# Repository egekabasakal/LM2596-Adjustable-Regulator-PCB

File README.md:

# LM2596 Adjustable Regulator PCB V0.1.0

Custom PCB design of an adjustable buck converter using LM2596S-ADJ.

## Features
- Input reverse-polarity protection (SB560 diode)
- Output LED indicator with series resistor
- Adjustable feedback via 3296W potentiometer
- Test pads for IN+/IN− and OUT+/OUT−
- 2-pin terminal blocks for input and output
- Barrel jack connector (optional)

## Files
- `schematic/` → KiCad schematic files
- `pcb/` → KiCad PCB layout
- `docs/` → images (schematic, layout, 3D)

## License
MIT

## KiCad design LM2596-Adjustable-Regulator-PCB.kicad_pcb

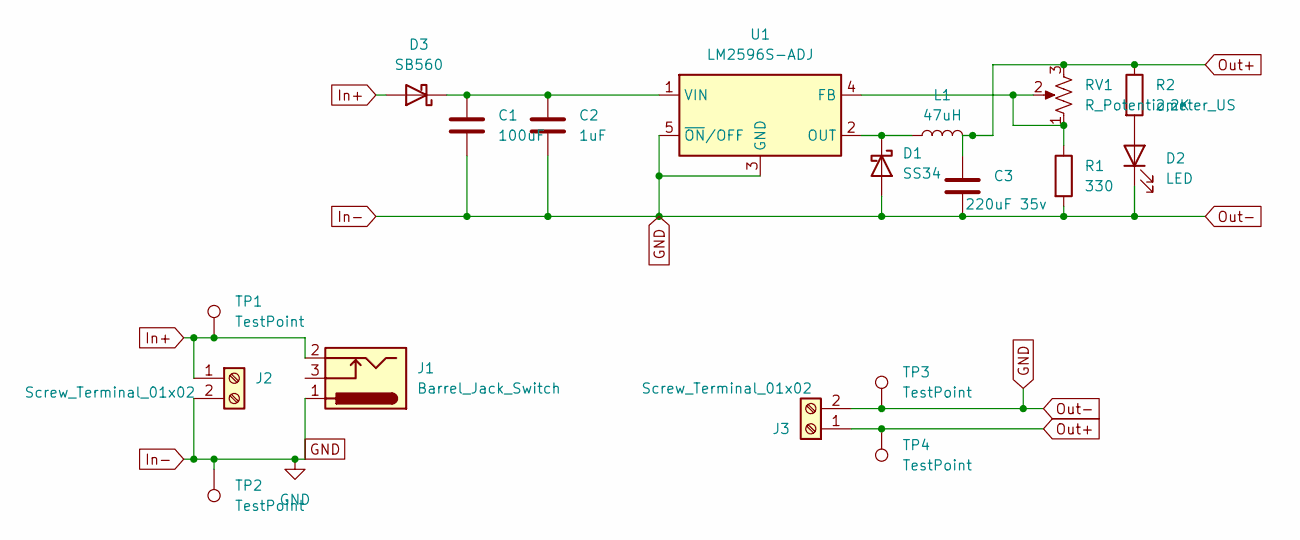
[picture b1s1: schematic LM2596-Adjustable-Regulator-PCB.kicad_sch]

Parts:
C1: 100uF; C_Elec_6.3x7.7
C2: 1uF; C_0805_2012Metric
C3: 220uF 35v; C_Elec_6.3x7.7
D1: SS34; D_SMA
D2: LED; LED_0201_0603Metric
D3: SB560; D_DO-201AD_P15.24mm_Horizontal
J1: Barrel_Jack_Switch; BarrelJack_CUI_PJ-063AH_Horizontal
J2, J3: Screw_Terminal_01x02; TerminalBlock_bornier-2_P5.08mm
L1: 47uH; L_12x12mm_H4.5mm
R1: 330; R_Axial_DIN0204_L3.6mm_D1.6mm_P2.54mm_Vertical
R2: 2,2K; R_Axial_DIN0204_L3.6mm_D1.6mm_P2.54mm_Vertical
RV1: R_Potentiometer_US; Potentiometer_Bourns_3269X_Horizontal
TP1, TP2, TP3, TP4: TestPoint; Pin_D1.4mm_L8.5mm_W2.8mm_FlatFork
U1: LM2596S-ADJ; TO-263-5_TabPin3

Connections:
GND: C1.2, C2.2, C3.2, D1.2 (A), D2.1 (K), J1.1, J2.2, J3.2, R1.2, TP2.1, TP3.1, U1.3 (GND), U1.5 (~ON/OFF)
In+: D3.2 (A), J1.2, J2.1, TP1.1
unnamed: D1.1 (K), L1.1, U1.2 (OUT)
unnamed: D2.2 (A), R2.2
unnamed: C1.1, C2.1, D3.1 (K), U1.1 (VIN)
unnamed: R1.1, RV1.1, RV1.2, U1.4 (FB)
Out+: C3.1, J3.1, L1.2, R2.1, RV1.3, TP4.1

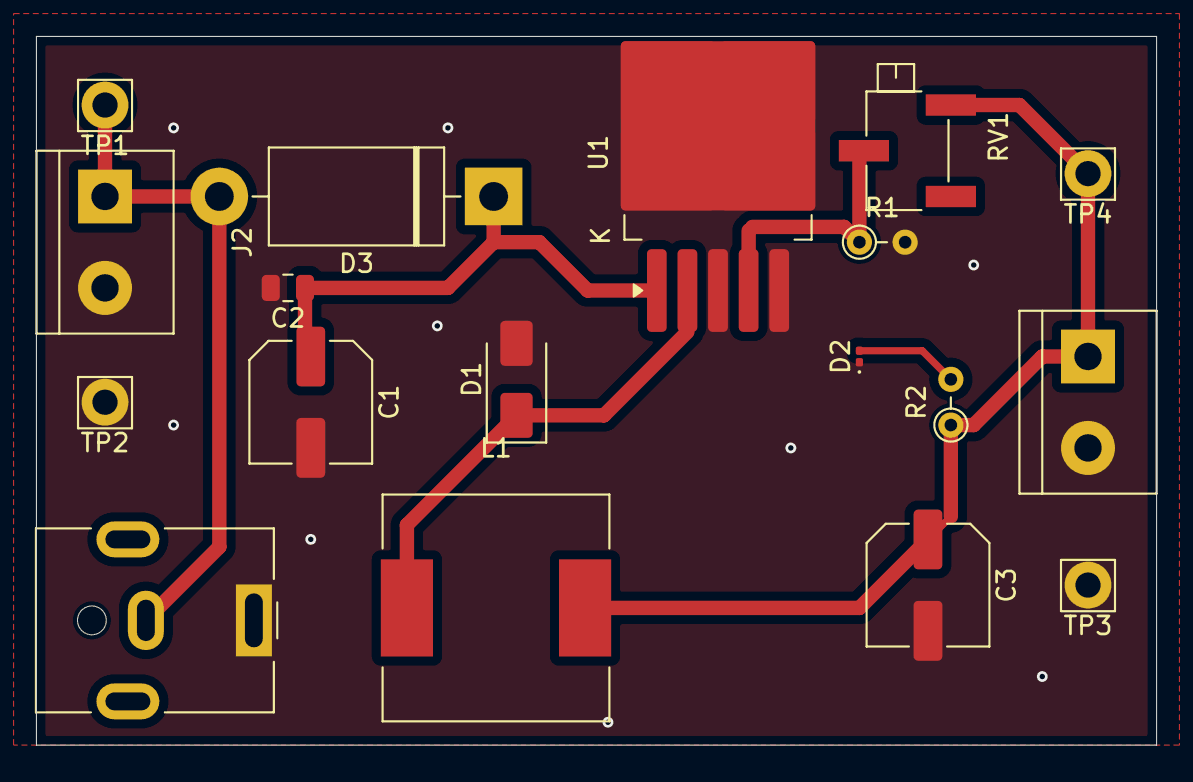
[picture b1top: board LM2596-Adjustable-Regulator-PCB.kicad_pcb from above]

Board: 2 copper layers, 62.2 x 39.4 mm, 18 parts (0 on the bottom side), 7 nets.

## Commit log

2025-09-07 Update LICENSE
2025-09-07 Add KiCad schematic and PCB files
    Initial commit of LM2596 adjustable regulator PCB design.
